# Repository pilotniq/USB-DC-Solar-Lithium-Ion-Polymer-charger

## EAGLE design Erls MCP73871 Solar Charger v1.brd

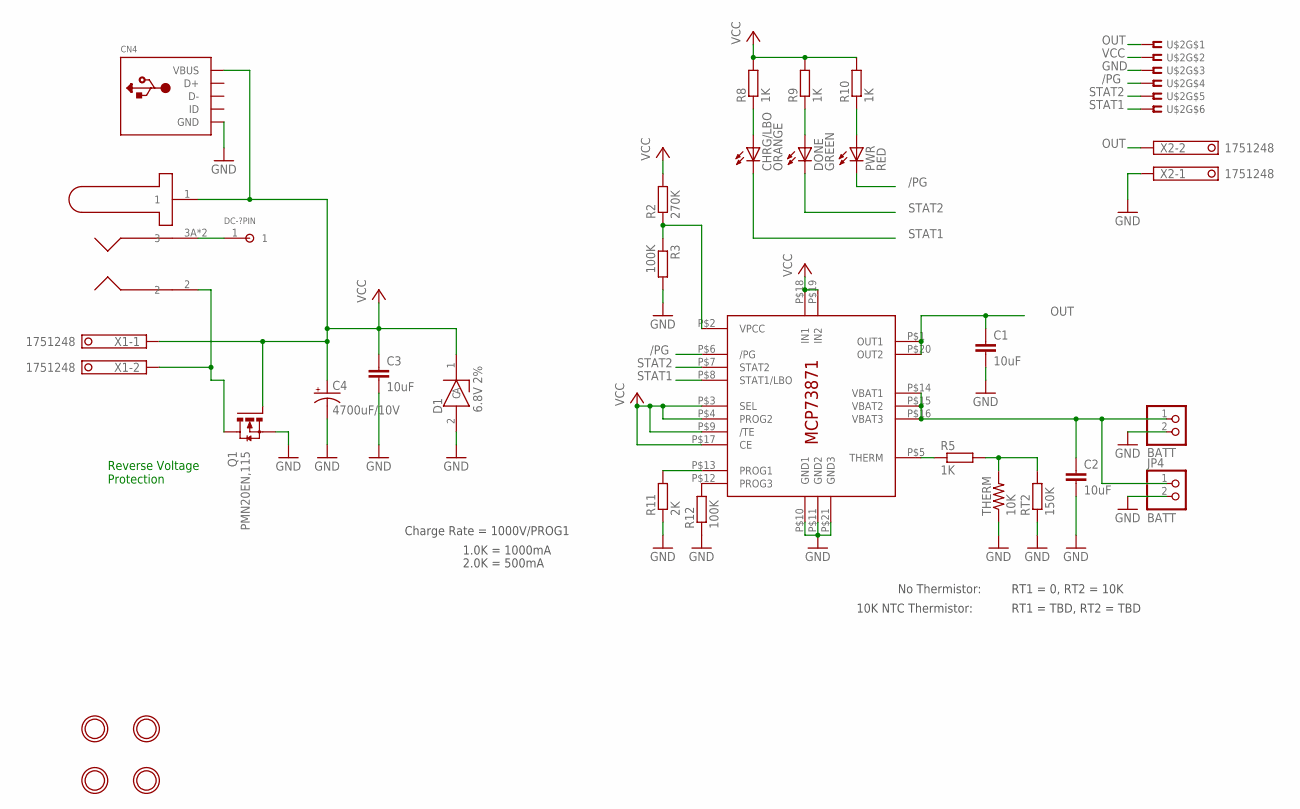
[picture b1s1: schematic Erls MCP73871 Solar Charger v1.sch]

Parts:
BATT: JST_2PIN-SMT-RA; JST-PH-2-SMT-RA
C1, C2, C3: 10uF; C0603K
C4: 4700uF/10V; E5-13
CHRG/LBO: ORANGE; CHIPLED_0603
CN4: USB-MINIB-ONSHORE-M26FTR
D1: 6.8V 2%; SOD323
DC-?PIN: PAD-1-TH
DONE: GREEN; CHIPLED_0603
JP4: BATT; 1X02_ROUND
PWR: RED; CHIPLED_0603
Q1: PMN20EN,115; SOT457R_PHILIPS
R2: 270K; R0603
R3, R12: 100K; R0603
R5, R8, R9, R10: 1K; R0603
R11: 2K; R0603
RT2: 150K; R0603
THERM: 10K; 0805-THM
U1: MCP73871; QFN20_4MM
U$1: DJACK-NOSW-CUI-PJ028-SMT; DCJACK-CUI-PJ028-SMT
U$2: FE06-1W-MOLEX-KK-22-15-2026; MOLEX-KK-22-15-2026-6
U$4, U$5, U$6, U$7: MOUNTINGHOLE2.5; MOUNTINGHOLE_2.5_PLATED
X1, X2: 1751248

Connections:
/PG: PWR.C, U1.P$6 (/PG), U$2.4
BATT: BATT.1 (2), C2.1, JP4.1, U1.P$14 (VBAT1), U1.P$15 (VBAT2), U1.P$16 (VBAT3)
DC-?PIN: DC-?PIN.1, U$1.3A (3), U$1.3B (3)
GND: BATT.2 (1), C1.2, C2.2, C3.2, C4.-, CN4.5 (GND), D1.2 (A), JP4.2, Q1.4 (S), R3.2, R11.1, R12.1, RT2.1, THERM.1, U1.P$10 (GND1), U1.P$11 (GND2), U1.P$21 (GND3), U$2.3, X2.1
INGND: Q1.1 (D), Q1.2 (D), Q1.5 (D), Q1.6 (D), U$1.2, X1.2
unnamed: R5.2, RT2.2, THERM.2
unnamed: CHRG/LBO.A, R8.1
unnamed: DONE.A, R9.1
unnamed: PWR.A, R10.1
unnamed: R12.2, U1.P$12 (PROG3)
unnamed: R11.2, U1.P$13 (PROG1)
OUT: C1.1, U1.P$1 (OUT1), U1.P$20 (OUT2), U$2.1, X2.2
STAT1: CHRG/LBO.C, U1.P$8 (STAT1/LBO), U$2.6
STAT2: DONE.C, U1.P$7 (STAT2), U$2.5
THERM: R5.1, U1.P$5 (THERM)
VCC: C3.1, C4.+, CN4.1 (VBUS), D1.1 (C), Q1.3 (G), R2.2, R8.2, R9.2, R10.2, U1.P$3 (SEL), U1.P$4 (PROG2), U1.P$9 (/TE), U1.P$17 (CE), U1.P$18 (IN1), U1.P$19 (IN2), U$1.1, U$2.2, X1.1
VPCC: R2.1, R3.1, U1.P$2 (VPCC)

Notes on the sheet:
Charge Rate = 1000V/PROG1
1.0K = 1000mA
2.0K = 500mA
No Thermistor:
10K NTC Thermistor:
RT1 = 0, RT2 = 10K
RT1 = TBD, RT2 = TBD
Reverse Voltage Protection

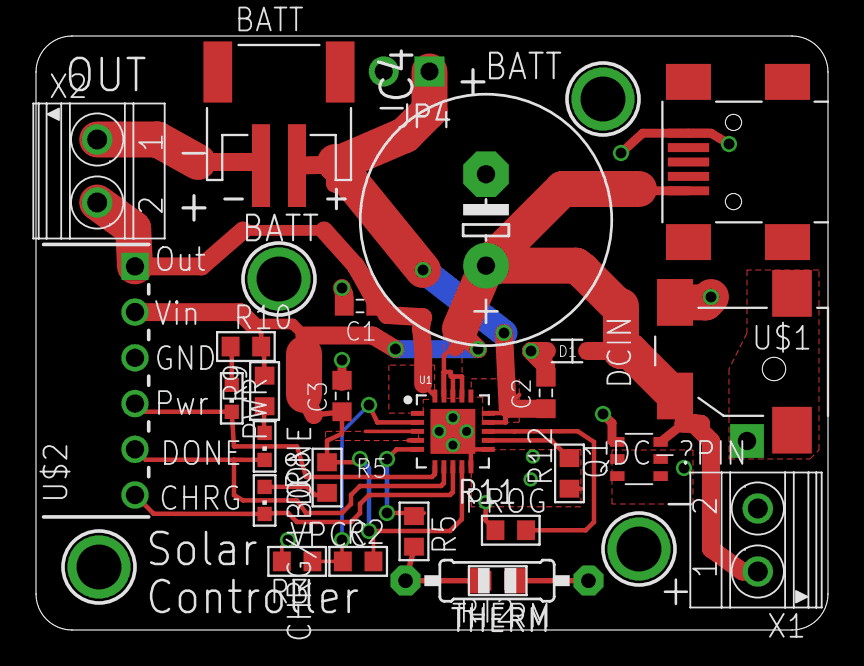
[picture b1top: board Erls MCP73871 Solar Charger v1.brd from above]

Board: 2 copper layers, 44.0 x 33.0 mm, 32 parts (0 on the bottom side), 17 nets.

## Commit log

2016-03-31 First commit of my modified boards.
    Zener diode for DC input over voltage protection (chip is fried by over 7V).
    Connectors:
    DC input: USB mini B, screw terminals, or DC jack
    Battery: JST or header pins
    Output: power and signals through 6-pin female angled header. Power also by screw terminals
    All configuration components at the bottom of the board.
